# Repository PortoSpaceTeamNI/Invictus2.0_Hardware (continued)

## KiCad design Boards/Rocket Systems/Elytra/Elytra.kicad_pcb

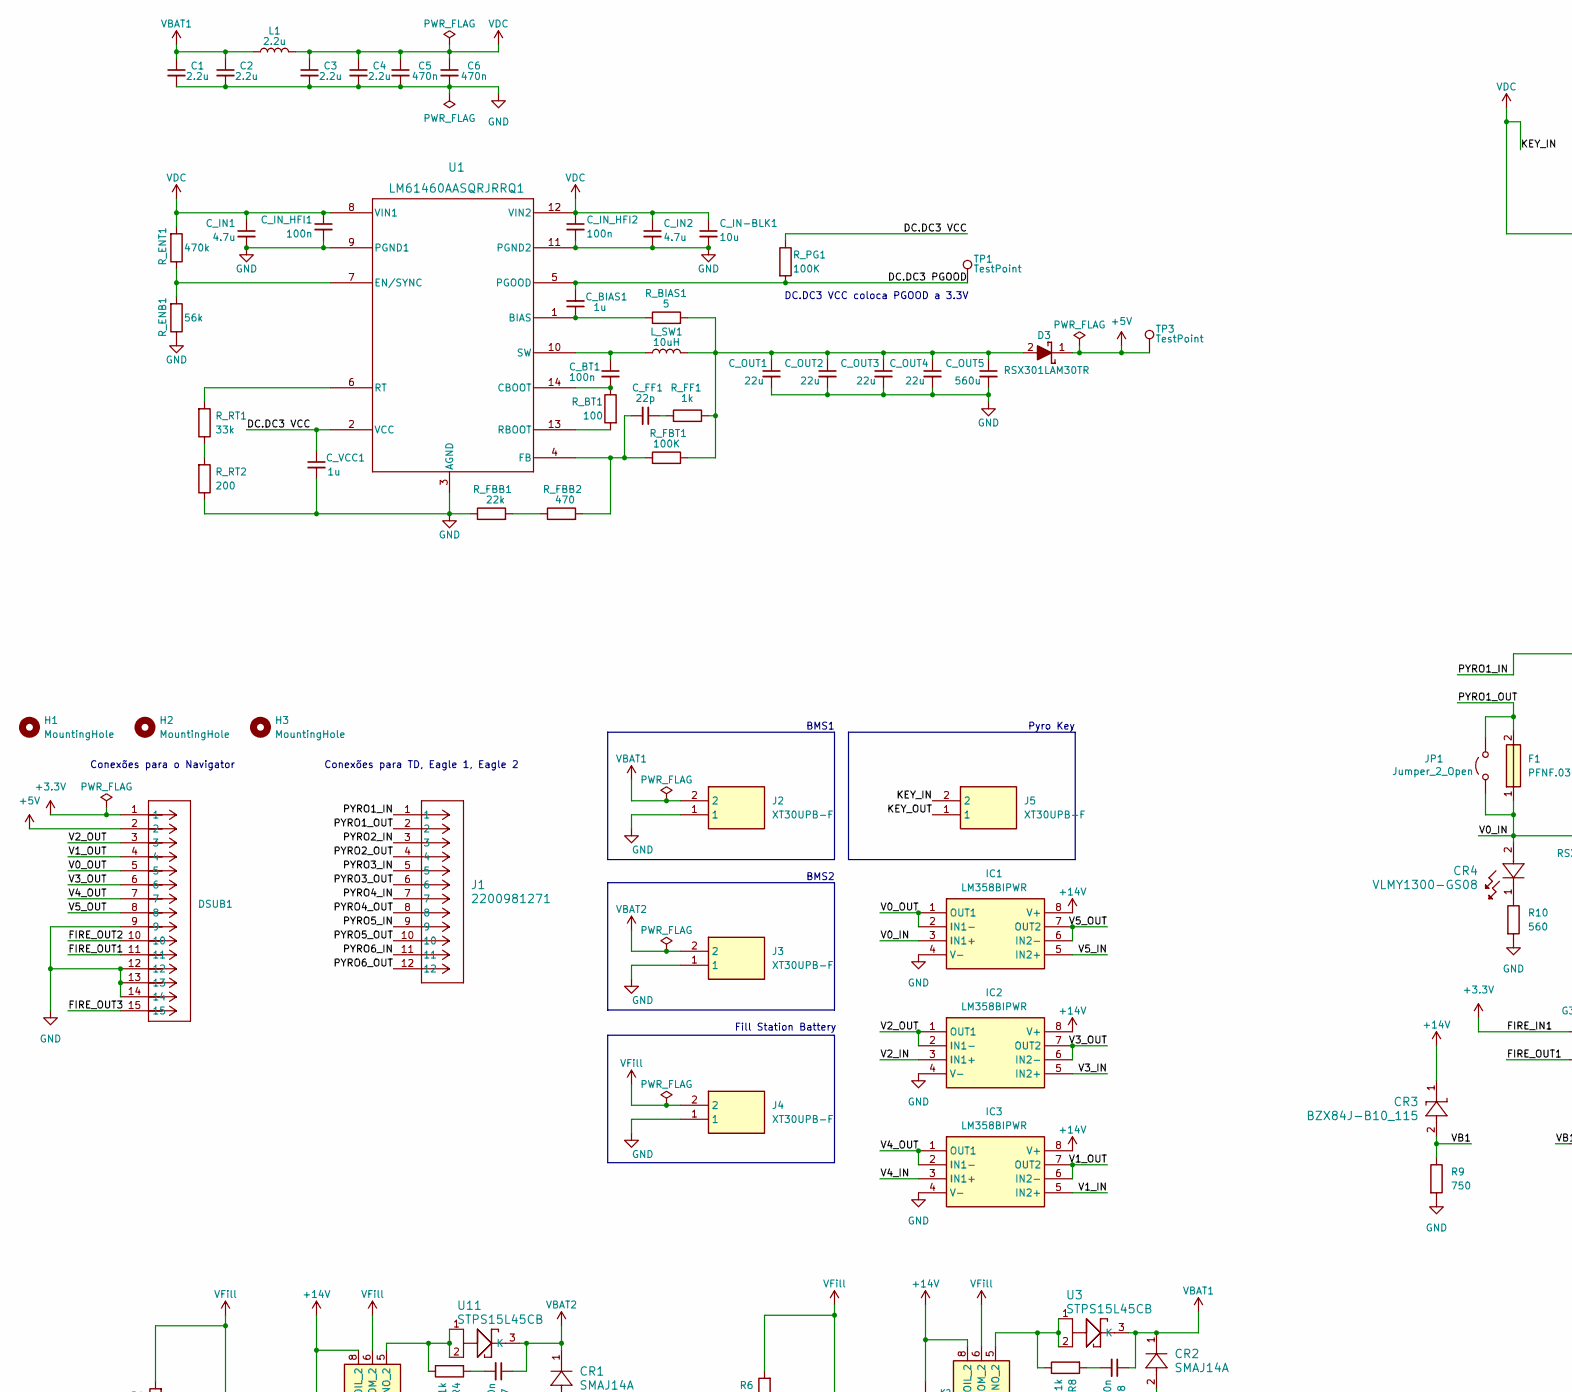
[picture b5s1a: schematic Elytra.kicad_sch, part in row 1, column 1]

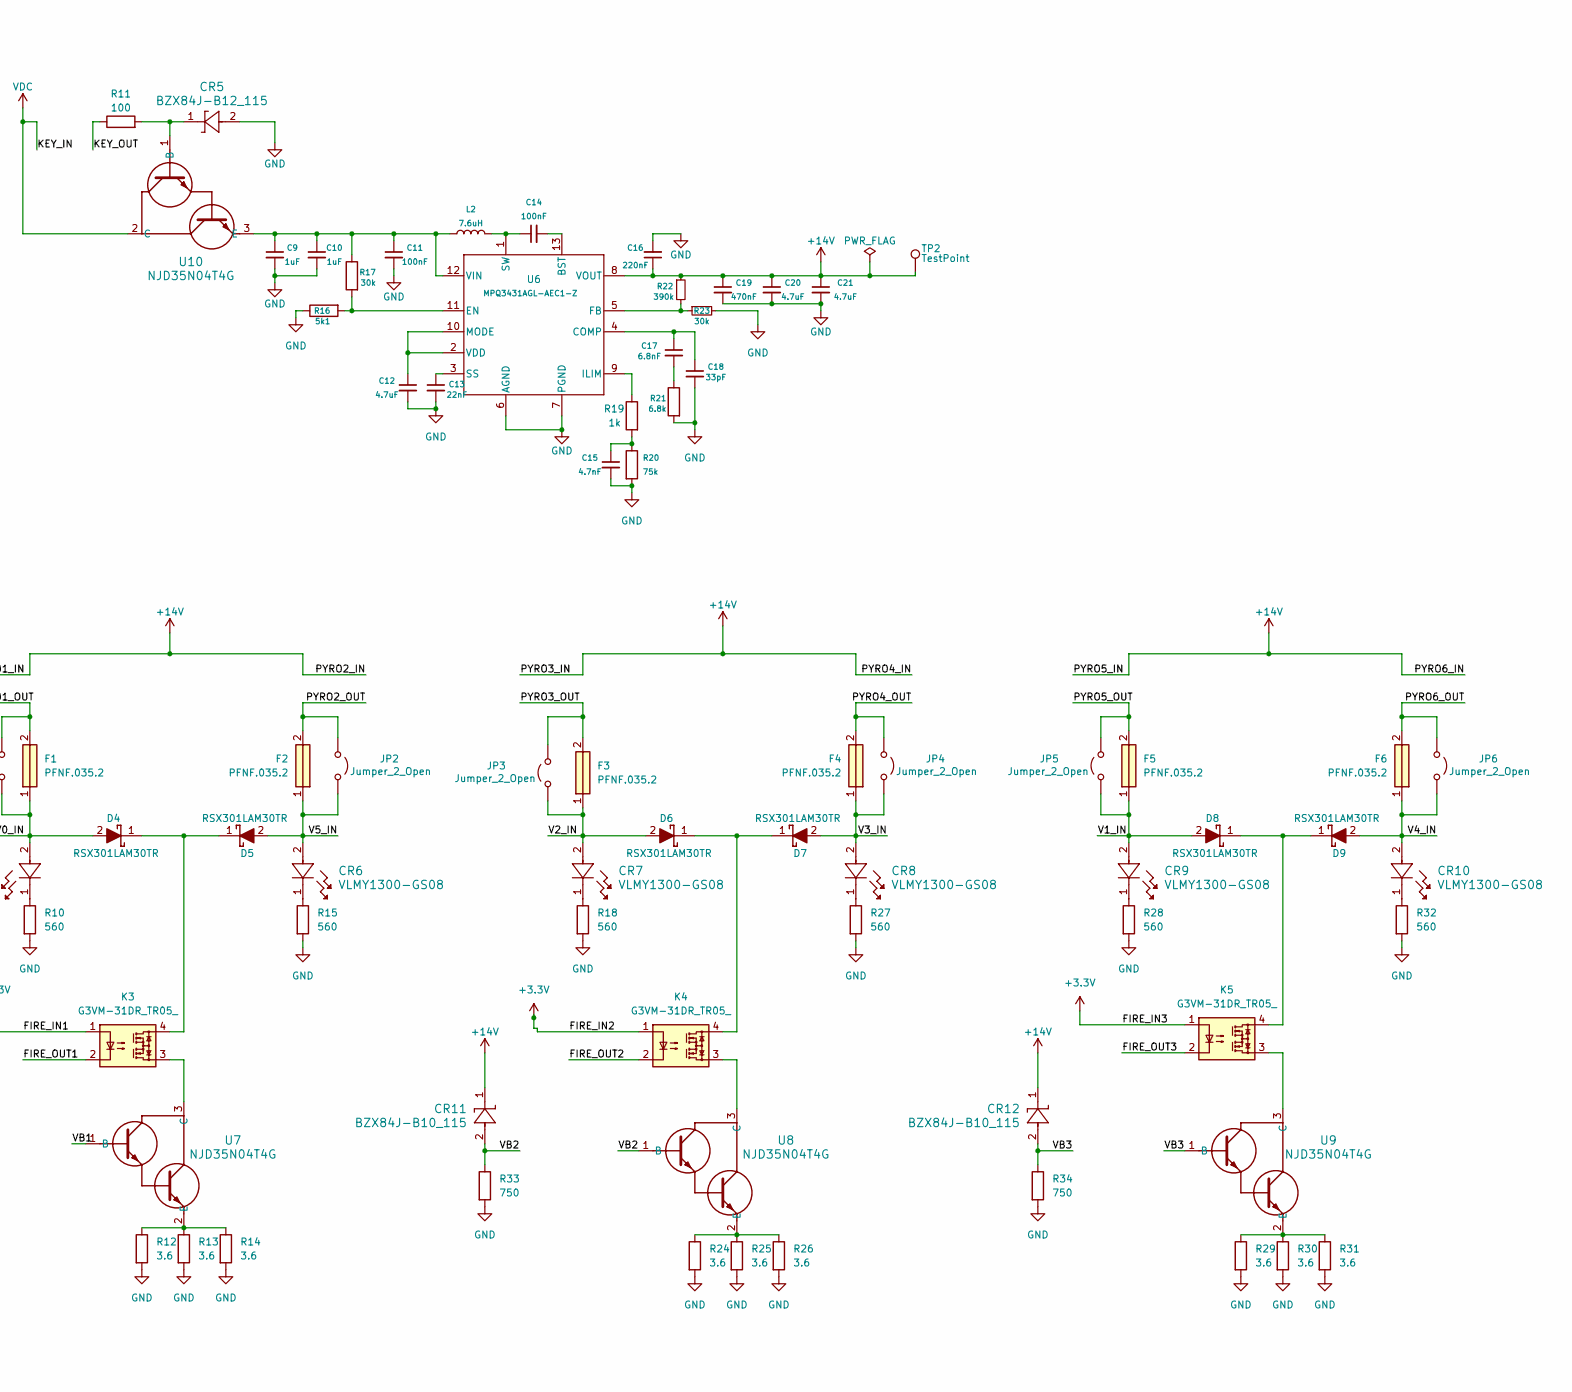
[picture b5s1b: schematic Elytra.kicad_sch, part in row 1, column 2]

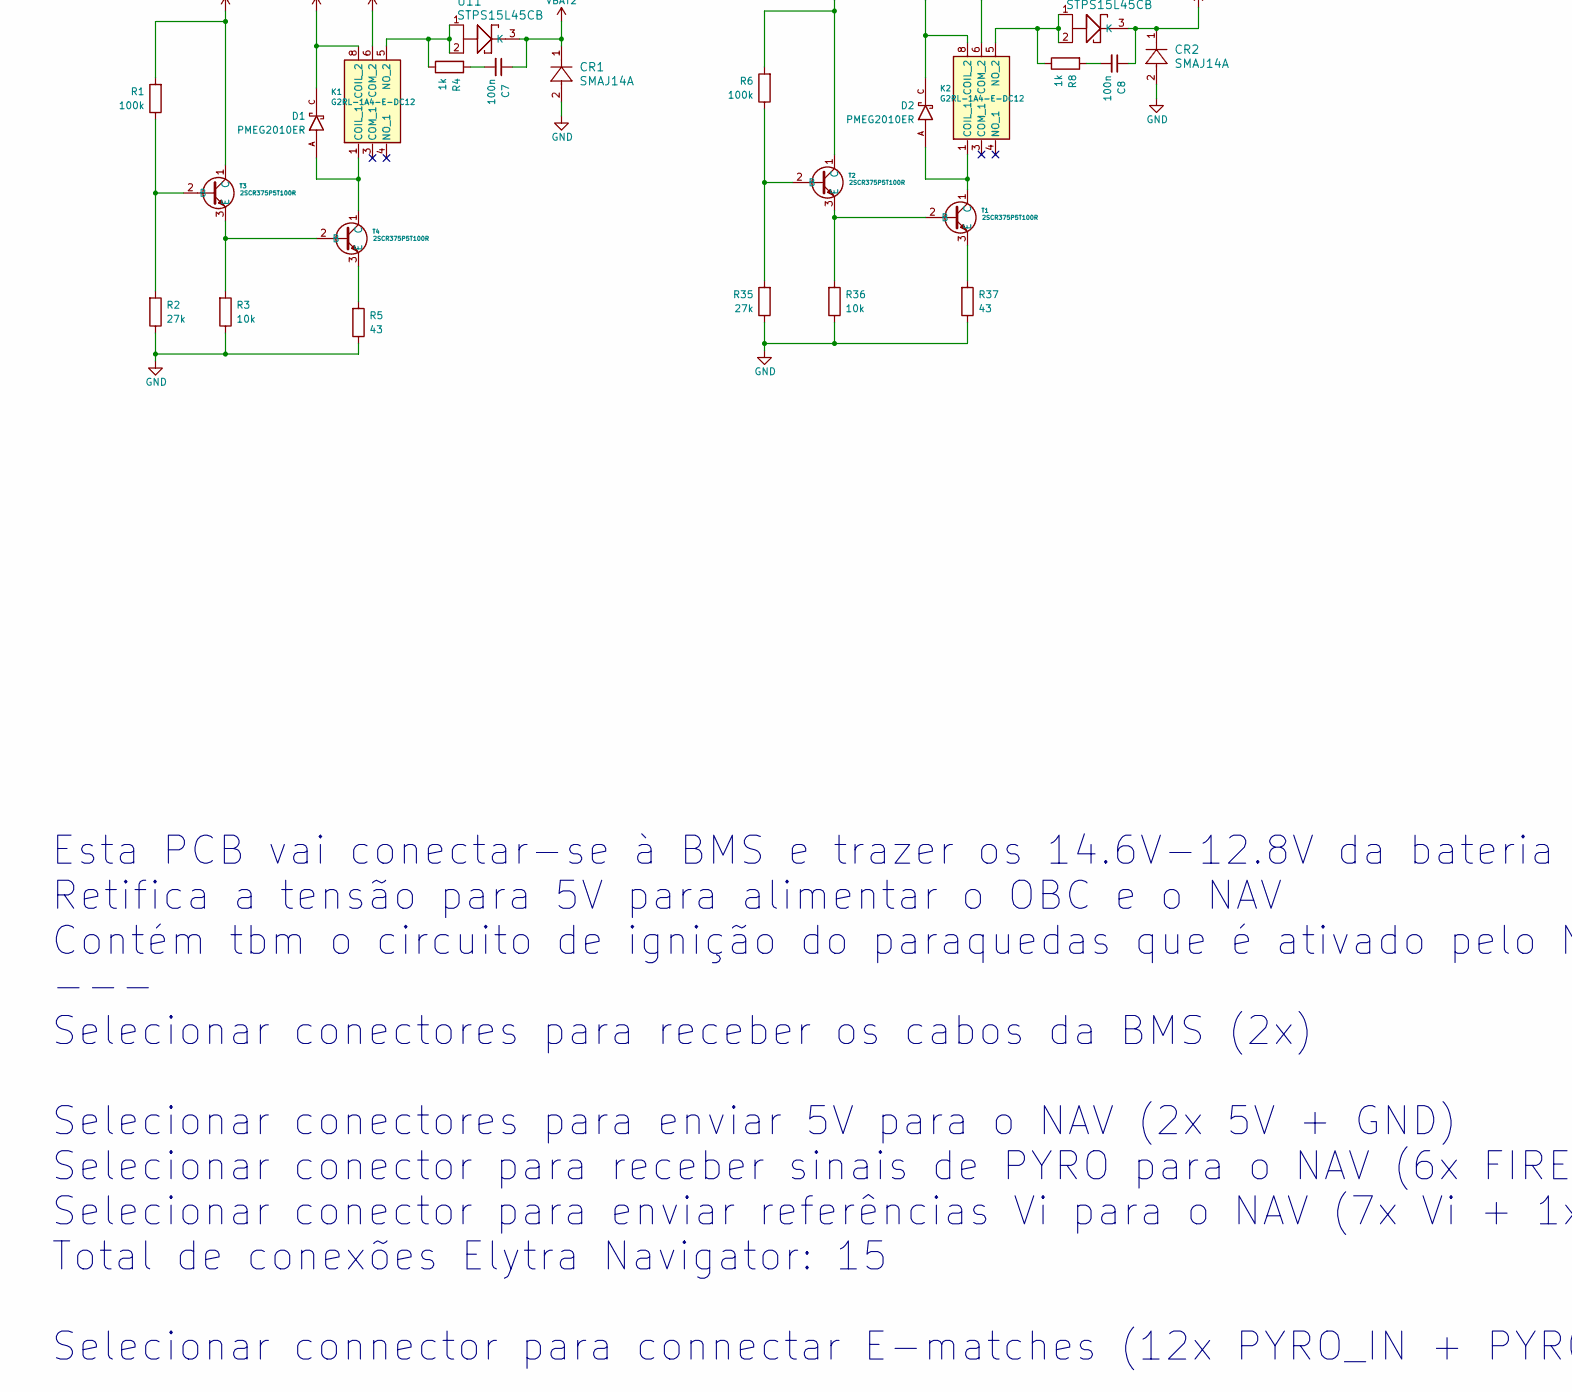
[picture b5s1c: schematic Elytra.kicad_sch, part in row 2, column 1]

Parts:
C1, C2, C3, C4: 2.2u; Capacitor_1206
C5, C6: 470n; Capacitor_1206
C7, C8: 100n; Capacitor_0603
C9, C10: 1uF; Capacitor_0603
C11, C14: 100nF; Capacitor_0603
C12: 4.7uF; Capacitor_0603
C13: 22nF; Capacitor_0603
C15: 4.7nF; Capacitor_0603
C16: 220nF; Capacitor_0603
C17: 6.8nF; Capacitor_0603
C18: 33pF; Capacitor_0603
C19: 470nF; Capacitor_0603
C20, C21: 4.7uF; Capacitor_0805
CR1, CR2: SMAJ14A; SMASeries_LTF
CR3, CR11, CR12: BZX84J-B10_115; CR_SC-90_NEX
CR4, CR6, CR7, CR8, CR9, CR10: VLMY1300-GS08; LEDC1608X100N
CR5: BZX84J-B12_115; CR_SC-90_NEX
C_BIAS1: 1u; Capacitor_0603
C_BT1: 100n; Capacitor_0603
C_FF1: 22p; Capacitor_0402
C_IN1, C_IN2: 4.7u; Capacitor_1206
C_IN-BLK1: 10u; Capacitor_4mm
C_IN_HFI1, C_IN_HFI2: 100n; Capacitor_0603
C_OUT1, C_OUT2, C_OUT3, C_OUT4: 22u; Capacitor_0805
C_OUT5: 560u; Capacitor_8mm
C_VCC1: 1u; Capacitor_0603
D1, D2: PMEG2010ER; SODFL3517X110N; PARTREV 01
D3, D4, D5, D6, D7, D8, D9: RSX301LAM30TR; DIOM5026X220N; Mouser Part Number 755-RSX301L-30DDTE25
DSUB1: HDL15-SL-B
F1, F2, F3, F4, F5, F6: PFNF.035.2; FUS1206_24N_SCH; Mouser Part Number 693-PFNF.035.2
H1, H2, H3: MountingHole; MountingHole_3.2mm_M3_ISO7380
IC1, IC2, IC3: LM358BIPWR; SOP65P640X120-8N; Mouser Part Number 595-LM358BIPWR
J1: 2200981271; CONN_2200980000-SD_12_MOL
J2, J3, J4, J5: XT30UPB-F; XT30UPBF; Manufacturer_Part_Number XT30UPB-F
JP1, JP2, JP3, JP4, JP5, JP6: Jumper_2_Open; SolderJumper-2_P1.3mm_Open_RoundedPad1.0x1.5mm
K1, K2: G2RL-1A4-E-DC12; G2RL1A4EDC12; Mouser Part Number 653-G2RL-1A4-E-DC12
K3, K4, K5: G3VM-31DR_TR05_; G3VM31DRTR05; Mouser Part Number 653-G3VM-31DR(TR05)
L1: 2.2u; IND_SPM10065VT-2R2M-D
L2: 7.6uH; IND_BOURNS_SRR1260
L_SW1: 10uH; SRP7028A3R3M
R1, R6: 100k; RES_0603
R2, R35: 27k; RES_0603
R3, R36: 10k; RES_0603
R4, R8: 1k; RES_0805
R5, R37: 43; RES_0603
R9, R33, R34: 750; RES_0805
R10, R15, R18, R27, R28, R32: 560; RES_0805
R11: 100; RES_0805
R12, R13, R14, R24, R25, R26, R29, R30, R31: 3.6; RESC3263X80N
R16: 5k1; RES_0603
R17, R23: 30k; RES_0603
R19: 1k; RES_0603
R20: 75k; RES_0603
R21: 6.8k; RES_0603
R22: 390k; RES_0603
R_BIAS1: 5; RES_0603
R_BT1: 100; RES_0603
R_ENB1: 56k; RES_0603
R_ENT1: 470k; RES_0603
R_FBB1: 22k; RES_0603
R_FBB2: 470; RES_0603
R_FBT1: 100K; RES_0603
R_FF1: 1k; RES_0603
R_PG1: 100K; RES_0603
R_RT1: 33k; RES_0603
R_RT2: 200; RES_0603
T1, T2, T3, T4: 2SCR375P5T100R; TRANS_2SA2071P_ROM
TP1, TP2, TP3: TestPoint; TestPoint_Pad_2.0x2.0mm
U1: LM61460AASQRJRRQ1; VQFN-HR14_RJR_TEX
U3, U11: STPS15L45CB; DPAK_STM
U6: MPQ3431AGL-AEC1-Z; QFN-13_MPQ3431A_MNP
U7, U8, U9, U10: NJD35N04T4G; DPAK-4_6P22X6P73_ONS

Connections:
+3.3V: DSUB1.1, K3.1, K4.1, K5.1
+5V: D3.1 (K), DSUB1.2, TP3.1
+14V: C16.1, C19.1, C20.1, C21.1, CR3.1, CR11.1, CR12.1, D1.C, D2.C, IC1.8 (V+), IC2.8 (V+), IC3.8 (V+), J1.1, J1.3, J1.5, J1.7, J1.9, J1.11, K1.8 (COIL_2), K2.8 (COIL_2), R22.1, TP2.1, U6.8 (VOUT)
/DC.DC3 PGOOD: C_BIAS1.2, R_PG1.2, TP1.1, U1.5 (PGOOD)
/DC.DC3 VCC: C_VCC1.1, R_PG1.1, U1.2 (VCC)
/FIRE_OUT1: DSUB1.11, K3.2
/FIRE_OUT2: DSUB1.10, K4.2
/FIRE_OUT3: DSUB1.15, K5.2
/KEY_OUT: J5.1, R11.1
/PYRO1_OUT: F1.2, J1.2, JP1.2 (B)
/PYRO2_OUT: F2.2, J1.4, JP2.2 (B)
/PYRO3_OUT: F3.2, J1.6, JP3.2 (B)
/PYRO4_OUT: F4.2, J1.8, JP4.2 (B)
/PYRO5_OUT: F5.2, J1.10, JP5.2 (B)
/PYRO6_OUT: F6.2, J1.12, JP6.2 (B)
/V0_IN: CR4.2, D4.2 (A), F1.1, IC1.3 (IN1+), JP1.1 (A)
/V0_OUT: DSUB1.5, IC1.1 (OUT1), IC1.2 (IN1-)
/V1_IN: CR9.2, D8.2 (A), F5.1, IC3.5 (IN2+), JP5.1 (A)
/V1_OUT: DSUB1.4, IC3.6 (IN2-), IC3.7 (OUT2)
/V2_IN: CR7.2, D6.2 (A), F3.1, IC2.3 (IN1+), JP3.1 (A)
/V2_OUT: DSUB1.3, IC2.1 (OUT1), IC2.2 (IN1-)
/V3_IN: CR8.2, D7.2 (A), F4.1, IC2.5 (IN2+), JP4.1 (A)
/V3_OUT: DSUB1.6, IC2.6 (IN2-), IC2.7 (OUT2)
/V4_IN: CR10.2, D9.2 (A), F6.1, IC3.3 (IN1+), JP6.1 (A)
/V4_OUT: DSUB1.7, IC3.1 (OUT1), IC3.2 (IN1-)
/V5_IN: CR6.2, D5.2 (A), F2.1, IC1.5 (IN2+), JP2.1 (A)
/V5_OUT: DSUB1.8, IC1.6 (IN2-), IC1.7 (OUT2)
/VB1: CR3.2, R9.1, U7.1 (B)
/VB2: CR11.2, R33.1, U8.1 (B)
/VB3: CR12.2, R34.1, U9.1 (B)
GND: C1.2, C2.2, C3.2, C4.2, C5.2, C6.2, C9.2, C10.2, C11.2, C12.2, C13.2, C15.2, C16.2, C18.2, C19.2, C20.2, C21.2, CR1.2, CR2.2, CR5.2, C_IN1.2, C_IN2.2, C_IN-BLK1.2, C_IN_HFI1.2, C_IN_HFI2.2, C_OUT1.2, C_OUT2.2, C_OUT3.2, C_OUT4.2, C_OUT5.2, C_VCC1.2, DSUB1.9, DSUB1.12, DSUB1.13, DSUB1.14, IC1.4 (V-), IC2.4 (V-), IC3.4 (V-), J2.1, J3.1, J4.1, R2.1, R3.1, R5.1, R9.2, R10.2, R12.2, R13.2, R14.2, R15.2, R16.1, R18.2, R20.2, R21.2, R23.2, R24.2, R25.2, R26.2, R27.2, R28.2, R29.2, R30.2, R31.2, R32.2, R33.2, R34.2, R35.1, R36.1, R37.1, R_ENB1.1, R_FBB1.1, R_RT2.1, U1.3 (AGND), U1.9 (PGND1), U1.11 (PGND2), U6.6 (AGND), U6.7 (PGND)
unnamed: C7.2, R4.2
unnamed: C8.2, R8.2
unnamed: C15.1, R19.2, R20.1
unnamed: C17.2, R21.1
unnamed: CR4.1, R10.1
unnamed: CR6.1, R15.1
unnamed: CR7.1, R18.1
unnamed: CR8.1, R27.1
unnamed: CR9.1, R28.1
unnamed: CR10.1, R32.1
unnamed: C_FF1.1, R_FF1.2
unnamed: C_OUT1.1, C_OUT2.1, C_OUT3.1, C_OUT4.1, C_OUT5.1, D3.2 (A), L_SW1.2, R_BIAS1.2, R_FBT1.1, R_FF1.1
unnamed: D4.1 (K), D5.1 (K), K3.4
unnamed: D6.1 (K), D7.1 (K), K4.4
unnamed: D8.1 (K), D9.1 (K), K5.4
unnamed: D1.A, K1.1 (COIL_1), T4.1 (C)
unnamed: K1.5 (NO_2), R4.1, U11.1, U11.2
unnamed: D2.A, K2.1 (COIL_1), T1.1 (C)
unnamed: K2.5 (NO_2), R8.1, U3.1, U3.2
unnamed: R_FBB1.2, R_FBB2.1
unnamed: R_RT1.1, R_RT2.2
unnamed: R36.2, T1.2 (B), T2.3 (E)
unnamed: R37.2, T1.3 (E)
unnamed: R6.1, R35.2, T2.2 (B)
unnamed: R1.1, R2.2, T3.2 (B)
unnamed: R3.2, T3.3 (E), T4.2 (B)
unnamed: R5.2, T4.3 (E)
unnamed: C_BIAS1.1, R_BIAS1.1, U1.1 (BIAS)
unnamed: C_BT1.2, R_BT1.1, U1.14 (CBOOT)
unnamed: R_ENB1.2, R_ENT1.1, U1.7 (EN/SYNC)
unnamed: C_FF1.2, R_FBB2.2, R_FBT1.2, U1.4 (FB)
unnamed: R_BT1.2, U1.13 (RBOOT)
unnamed: R_RT1.2, U1.6 (RT)
unnamed: C_BT1.1, L_SW1.1, U1.10 (SW)
unnamed: C14.2, U6.13 (BST)
unnamed: C17.1, C18.1, U6.4 (COMP)
unnamed: R16.2, R17.2, U6.11 (EN)
unnamed: R22.2, R23.1, U6.5 (FB)
unnamed: R19.1, U6.9 (ILIM)
unnamed: C12.1, U6.2 (VDD), U6.10 (MODE)
unnamed: C13.1, U6.3 (SS)
unnamed: C14.1, L2.2, U6.1 (SW)
unnamed: K3.3, U7.3 (C)
unnamed: R12.1, R13.1, R14.1, U7.2 (E)
unnamed: K4.3, U8.3 (C)
unnamed: R24.1, R25.1, R26.1, U8.2 (E)
unnamed: K5.3, U9.3 (C)
unnamed: R29.1, R30.1, R31.1, U9.2 (E)
unnamed: CR5.1, R11.2, U10.1 (B)
unnamed: C9.1, C10.1, C11.1, L2.1, R17.1, U6.12 (VIN), U10.3 (E)
VBAT1: C1.1, C2.1, C8.1, CR2.1, J2.2, L1.1, U3.3 (K)
VBAT2: C7.1, CR1.1, J3.2, U11.3 (K)
VDC: C3.1, C4.1, C5.1, C6.1, C_IN1.1, C_IN2.1, C_IN-BLK1.1, C_IN_HFI1.1, C_IN_HFI2.1, J5.2, L1.2, R_ENT1.2, U1.8 (VIN1), U1.12 (VIN2), U10.2 (C)
VFill: J4.2, K1.6 (COM_2), K2.6 (COM_2), R1.2, R6.2, T2.1 (C), T3.1 (C)

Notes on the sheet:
Fill Station Battery
Conexões para o Navigator
DC.DC3 VCC coloca PGOOD a 3.3V
BMS1
BMS2
Pyro Key
Conexões para TD, Eagle 1, Eagle 2
Esta PCB vai conectar-se à BMS e trazer os 14.6V-12.8V da bateria Retifica a tensão para 5V para alimentar o OBC e o NAV Contém tbm o circuito de ignição do paraquedas que é ativado pelo NAV --- Selecionar conectores para receber os cabos da BMS (2x) Selecionar conectores para enviar 5V para o NAV 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

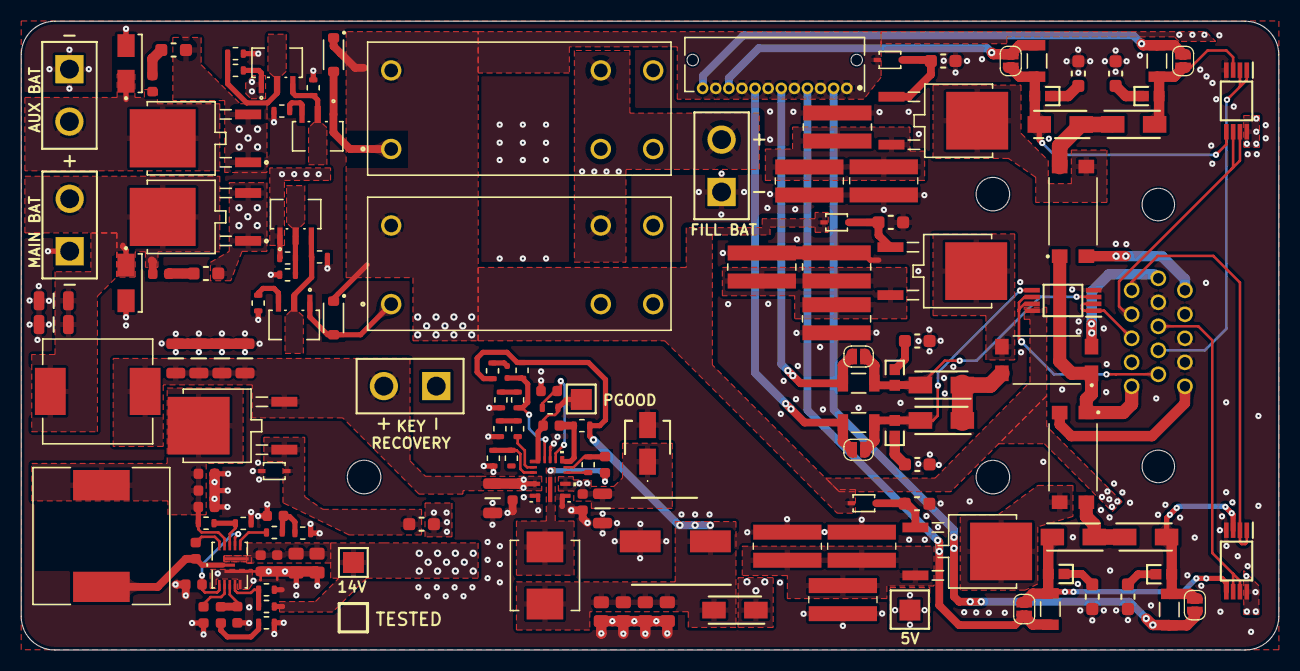
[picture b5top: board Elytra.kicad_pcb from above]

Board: 4 copper layers, 120.0 x 60.0 mm, 150 parts (0 on the bottom side), 85 nets.

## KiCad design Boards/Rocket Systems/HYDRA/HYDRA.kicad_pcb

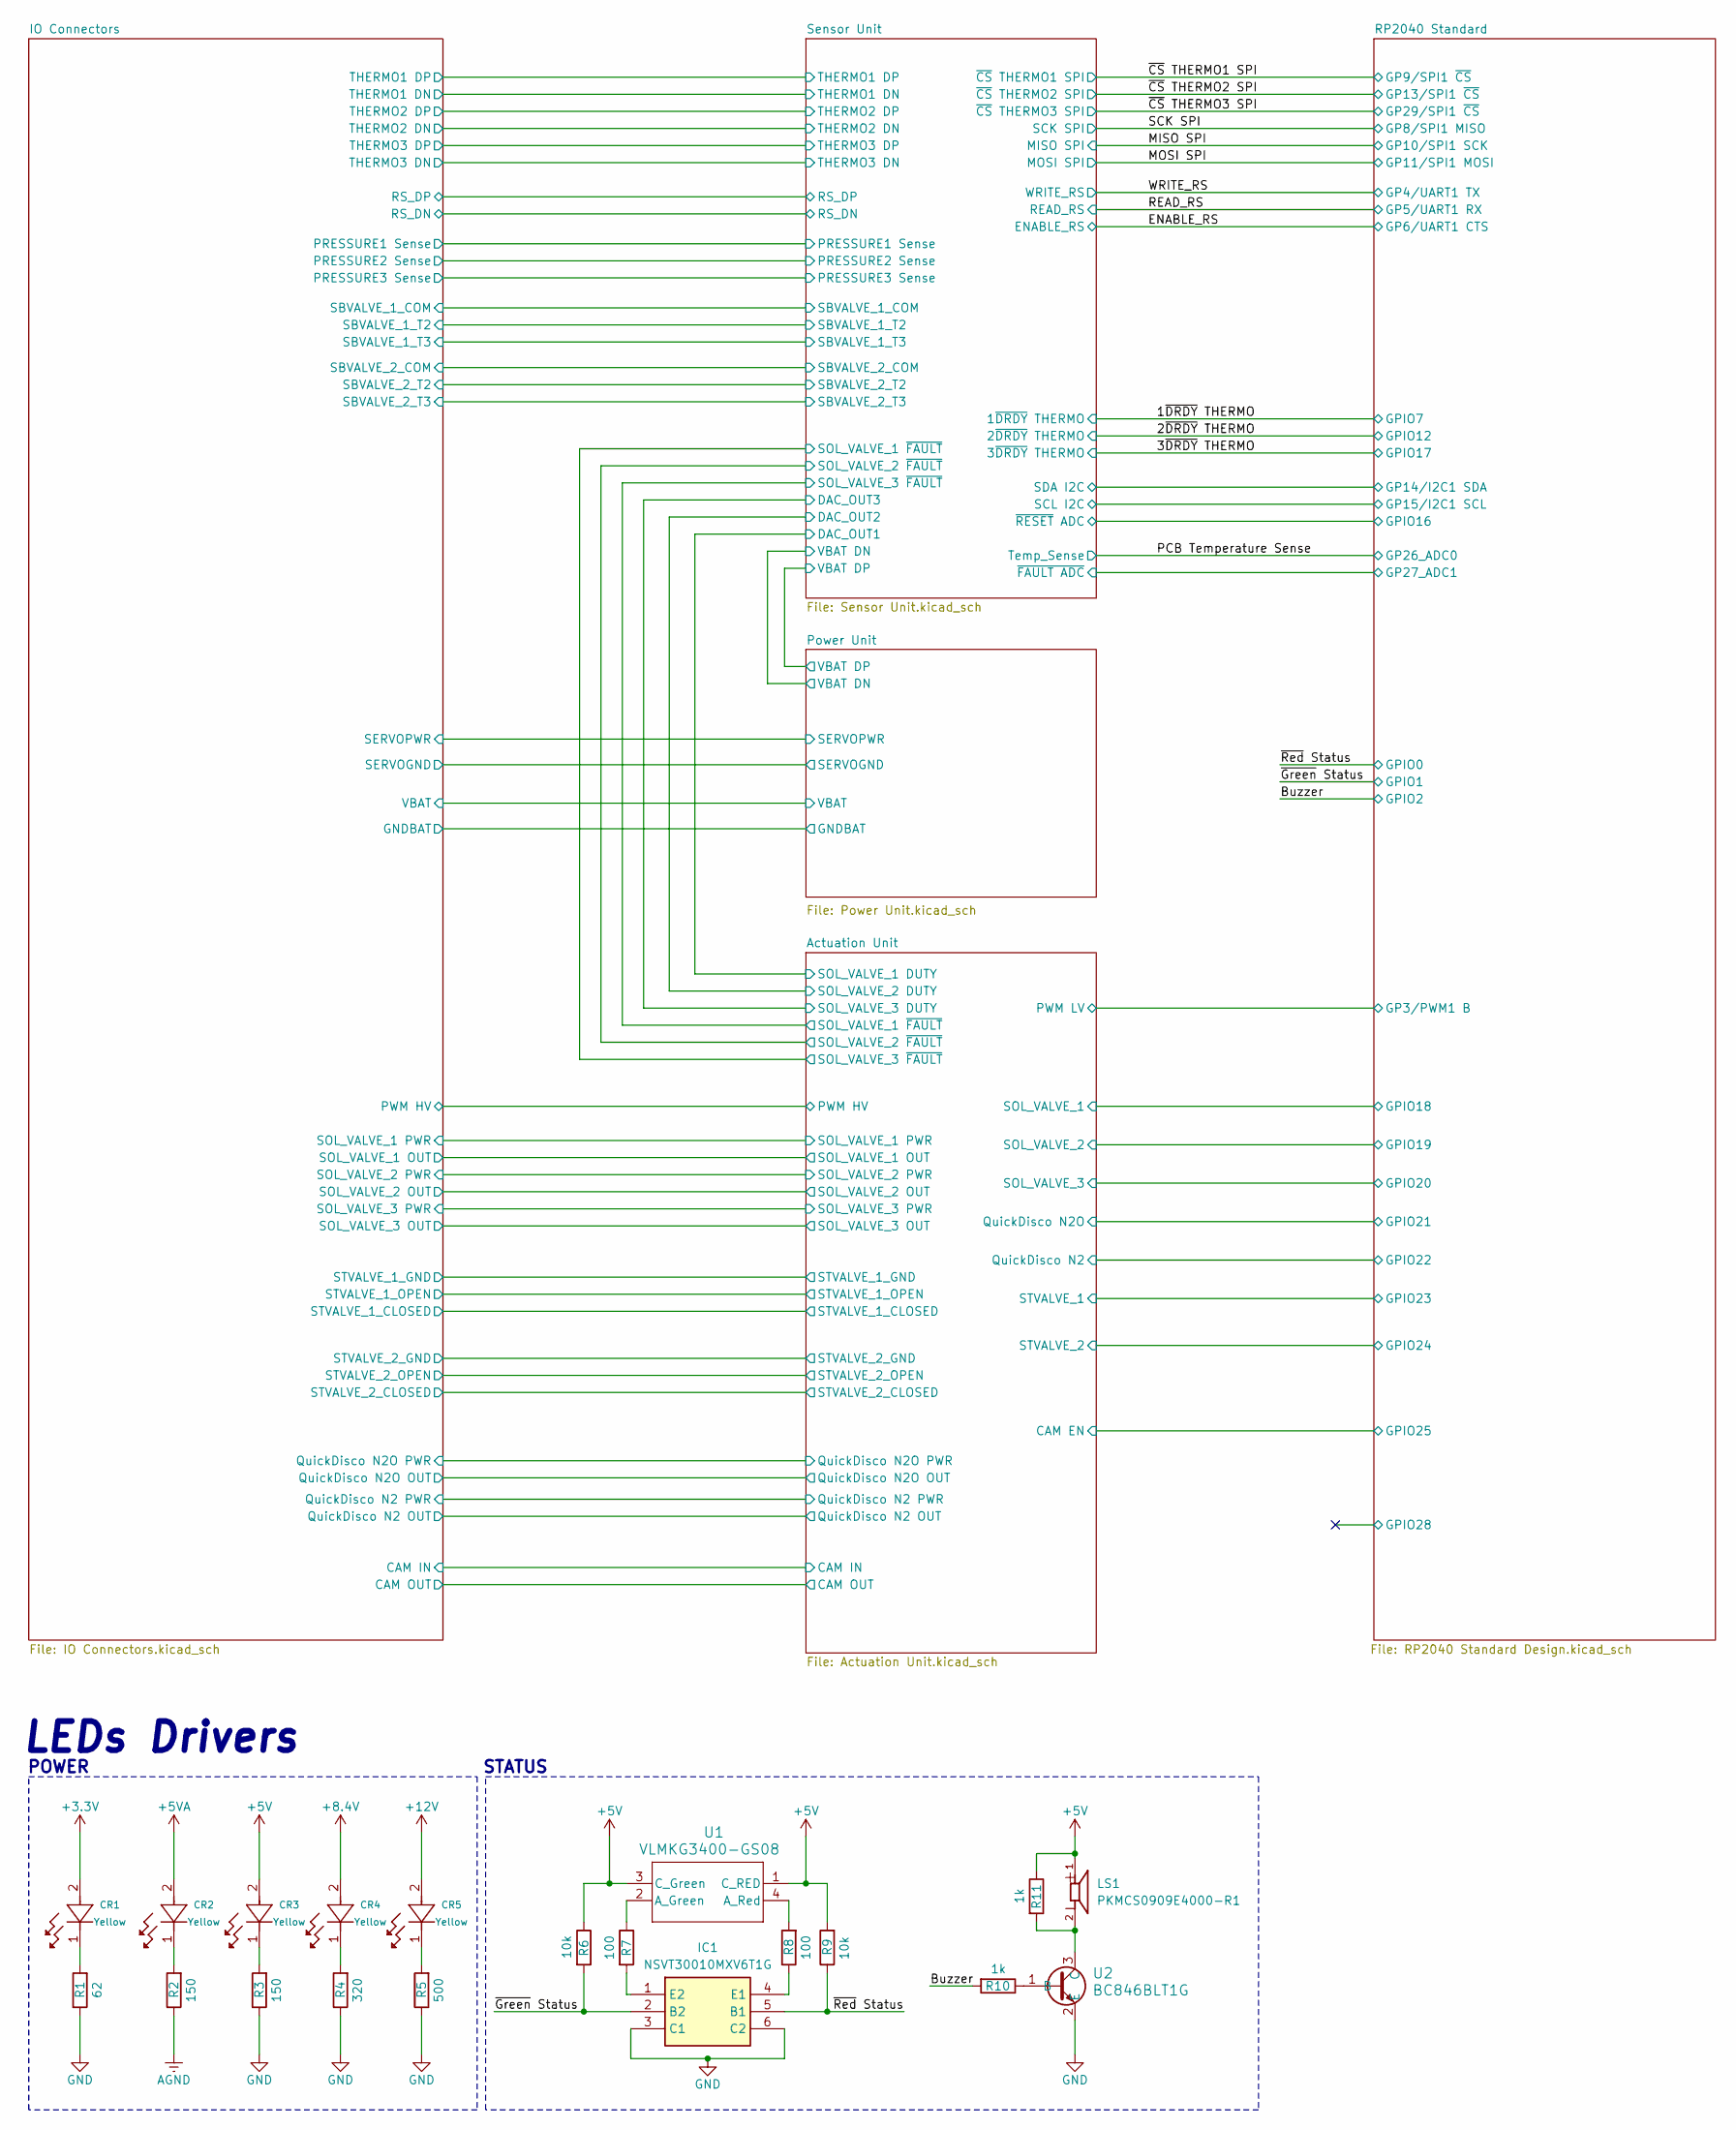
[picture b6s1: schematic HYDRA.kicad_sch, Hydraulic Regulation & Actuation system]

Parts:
CR1, CR2, CR3, CR4, CR5: VLMY1300-GS08; LEDC1608X100N
IC1: NSVT30010MXV6T1G; SOTFL50P160X60-6N; Mouser Part Number 863-NSVT30010MXV6T1G
LS1: PKMCS0909E4000-R1; SPKR_PKMCS0909E4000-R1; PARTREV May 22, 2020
R1: 62; RES_0603
R2, R3: 150; RES_0603
R4: 320; RES_0603
R5: 500; RES_0603
R6, R9: 10k; RES_0402
R7, R8: 100; RES_0603
R10, R11: 1k; RES_0603
U1: VLMKG3400-GS08; SMT_00-GS08_VIS
U2: BC846BLT1G; SOT-23_ONS

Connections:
+3.3V: CR1.2; also elsewhere on the board
+5V: CR3.2, LS1.1, R6.1, R9.2, R11.1, U1.1 (C_RED), U1.3 (C_Green); also elsewhere on the board
+5VA: CR2.2; also elsewhere on the board
+8.4V: CR4.2; also elsewhere on the board
+12V: CR5.2; also elsewhere on the board
/Buzzer: R10.2; also elsewhere on the board
/~Green Status: IC1.2 (B2), R6.2; also elsewhere on the board
/~Red Status: IC1.5 (B1), R9.1; also elsewhere on the board
AGND: R2.1; also elsewhere on the board
GND: IC1.3 (C1), IC1.6 (C2), R1.1, R3.1, R4.1, R5.1, U2.2 (E); also elsewhere on the board
unnamed: CR1.1, R1.2
unnamed: CR2.1, R2.2
unnamed: CR3.1, R3.2
unnamed: CR4.1, R4.2
unnamed: CR5.1, R5.2
unnamed: IC1.4 (E1), R8.1
unnamed: IC1.1 (E2), R7.2
unnamed: R7.1, U1.2 (A_Green)
unnamed: R8.2, U1.4 (A_Red)
unnamed: R10.1, U2.1 (B)
unnamed: LS1.2, R11.2, U2.3 (C)

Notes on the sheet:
POWER
LEDs Drivers
STATUS

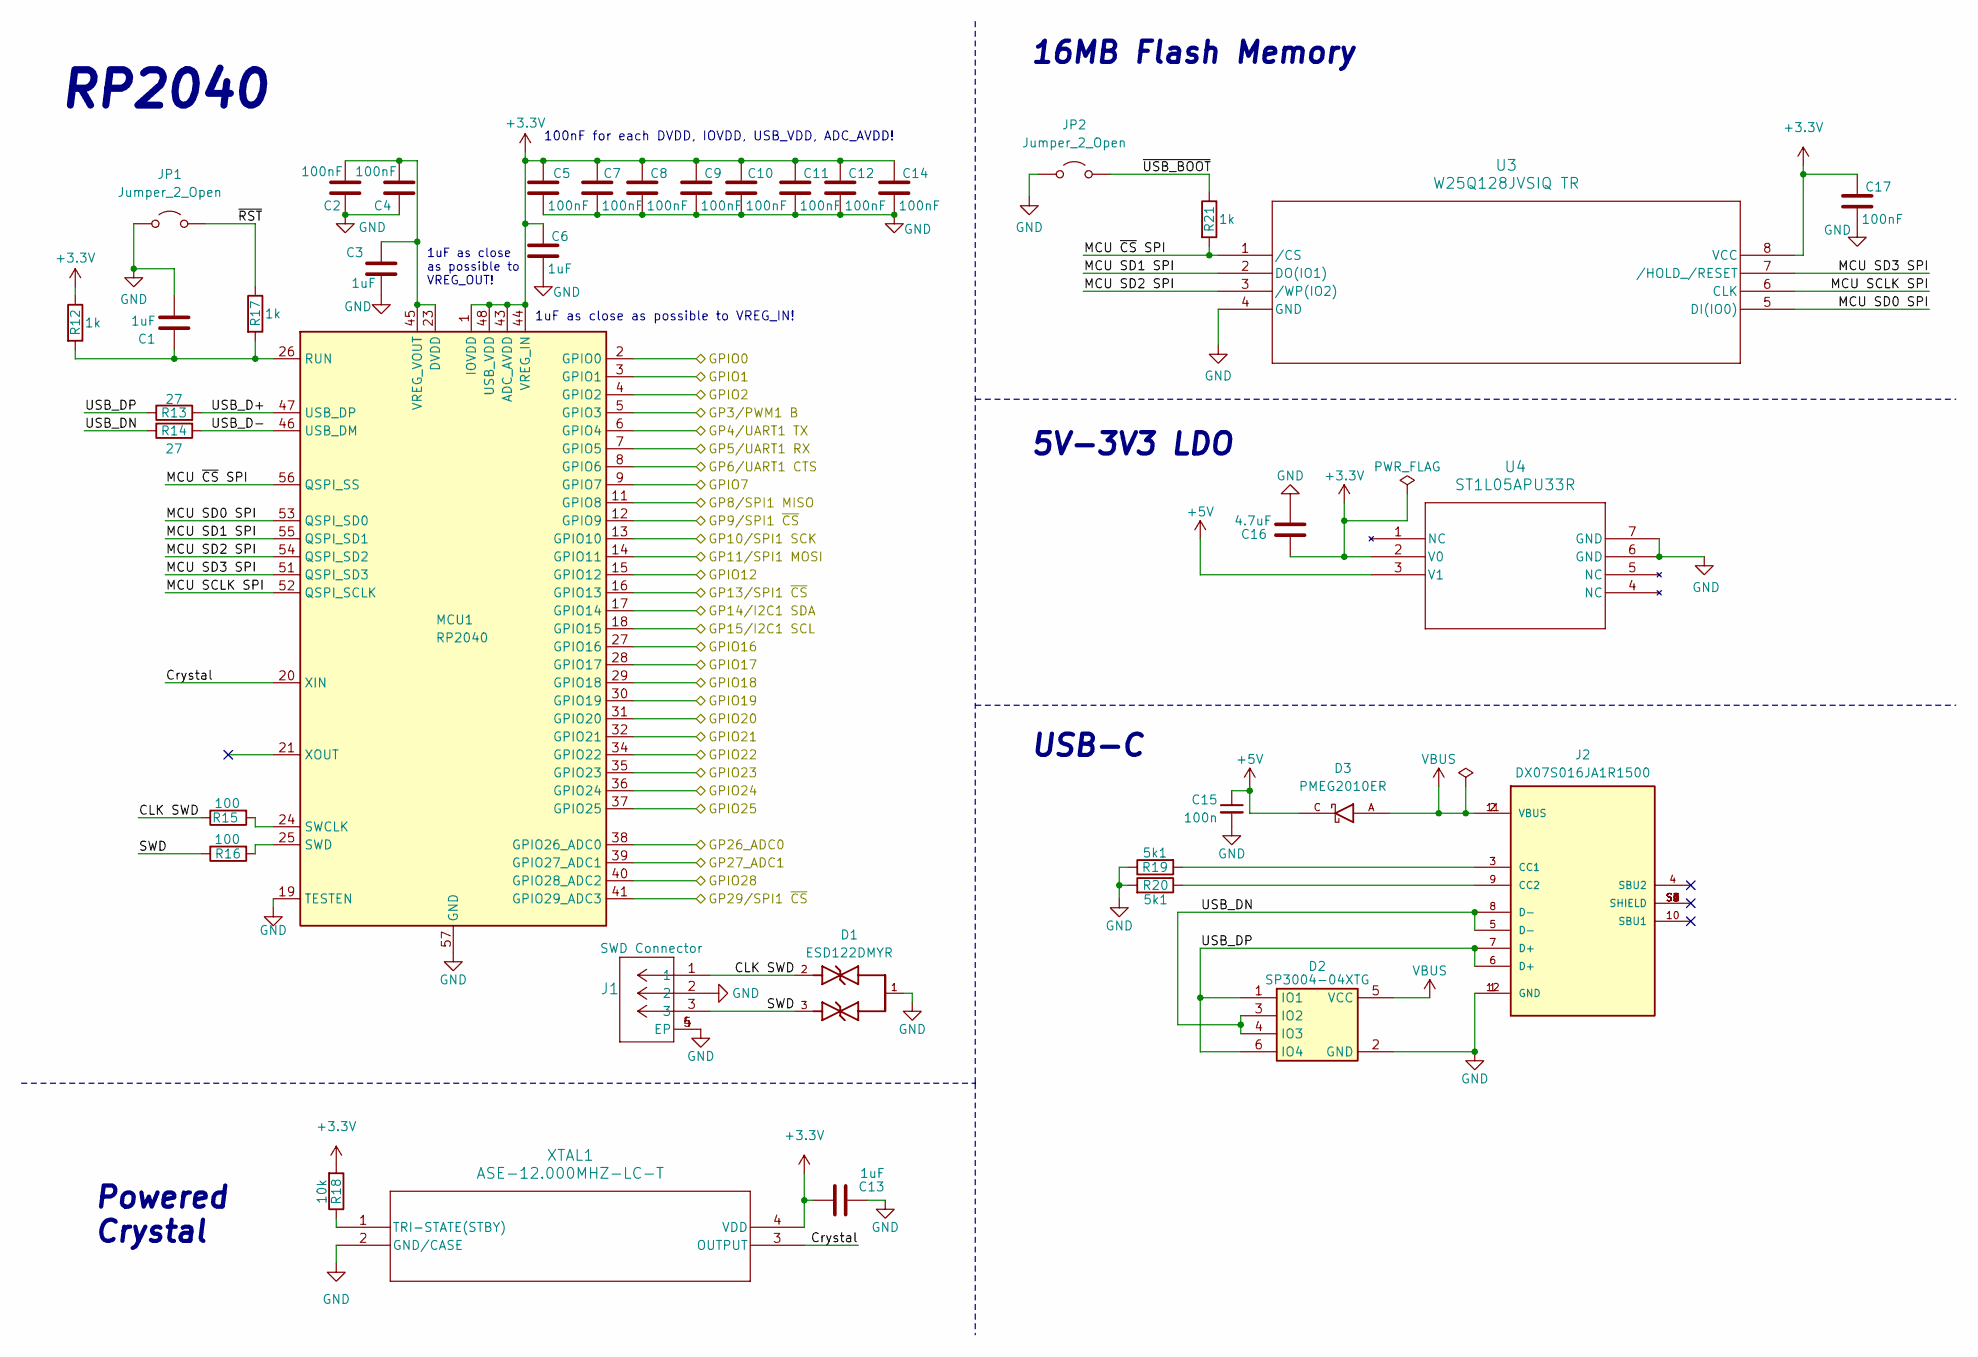
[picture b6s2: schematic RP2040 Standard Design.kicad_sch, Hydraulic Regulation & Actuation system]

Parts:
C1, C3, C6, C13: 1uF; Capacitor_0402
C2, C4, C5, C7, C8, C9, C10, C11, C12, C14, C17: 100nF; Capacitor_0402
C15: 100n; Capacitor_0402
C16: 4.7uF; Capacitor_0603
D1: ESD122DMYR; DIO_ESD122DMYR; PARTREV A
D2: SP3004-04XTG; SOT563_LTF; Mouser Part Number 576-SP3004-04XTG
D3: PMEG2010ER; SODFL3517X110N; PARTREV 01
J1: BM03B-SRSS-TBLFSN; CONN_BM03B-SRSS-TBLFSN_JST
J2: DX07S016JA1R1500; JAE_DX07S016JA1R1500; PARTREV 1
JP1, JP2: Jumper_2_Open; SolderJumper-2_P1.3mm_Open_RoundedPad1.0x1.5mm
MCU1: RP2040; QFN56_7X7_RPI
R12, R17, R21: 1k; RES_0402
R13, R14: 27; RES_0402
R15, R16: 100; RES_0402
R18: 10k; RES_0402
R19, R20: 5k1; RES_0402
U3: W25Q128JVSIQ TR; SOIC_208MIL_WIN
U4: ST1L05APU33R; DFN_5APU33R_STM
XTAL1: ASE-12.000MHZ-LC-T; ASE24576MHZLCT

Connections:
+3.3V: C5.1, C6.1, C7.1, C8.1, C9.1, C10.1, C11.1, C12.1, C13.1, C14.1, C16.2, C17.1, MCU1.1 (IOVDD), MCU1.10 (IOVDD), MCU1.22 (IOVDD), MCU1.33 (IOVDD), MCU1.42 (IOVDD), MCU1.43 (ADC_AVDD), MCU1.44 (VREG_IN), MCU1.48 (USB_VDD), MCU1.49 (IOVDD), R12.1, R18.2, U3.8 (VCC), U4.2 (V0), XTAL1.4 (VDD); also elsewhere on the board
+5V: C15.1, D3.C, U4.3 (V1); also elsewhere on the board
/1~DRDY THERMO: MCU1.9 (GPIO7); also elsewhere on the board
/2~DRDY THERMO: MCU1.15 (GPIO12); also elsewhere on the board
/3~DRDY THERMO: MCU1.28 (GPIO17); also elsewhere on the board
/Actuation Unit/CAM EN: MCU1.37 (GPIO25); also elsewhere on the board
/Actuation Unit/PWM LV: MCU1.5 (GPIO3); also elsewhere on the board
/Actuation Unit/QuickDisco N2: MCU1.34 (GPIO22); also elsewhere on the board
/Actuation Unit/QuickDisco N2O: MCU1.32 (GPIO21); also elsewhere on the board
/Actuation Unit/SOL_VALVE_1: MCU1.29 (GPIO18); also elsewhere on the board
/Actuation Unit/SOL_VALVE_2: MCU1.30 (GPIO19); also elsewhere on the board
/Actuation Unit/SOL_VALVE_3: MCU1.31 (GPIO20); also elsewhere on the board
/Actuation Unit/STVALVE_1: MCU1.35 (GPIO23); also elsewhere on the board
/Actuation Unit/STVALVE_2: MCU1.36 (GPIO24); also elsewhere on the board
/Buzzer: MCU1.4 (GPIO2); also elsewhere on the board
/ENABLE_RS: MCU1.8 (GPIO6); also elsewhere on the board
/MISO SPI: MCU1.13 (GPIO10); also elsewhere on the board
/MOSI SPI: MCU1.14 (GPIO11); also elsewhere on the board
/PCB Temperature Sense: MCU1.38 (GPIO26_ADC0); also elsewhere on the board
/READ_RS: MCU1.7 (GPIO5); also elsewhere on the board
/RP2040 Standard/CLK SWD: D1.2, J1.1, R15.1
/RP2040 Standard/Crystal: MCU1.20 (XIN), XTAL1.3 (OUTPUT)
/RP2040 Standard/GP14/I2C1 SDA: MCU1.17 (GPIO14); also elsewhere on the board
/RP2040 Standard/GP15/I2C1 SCL: MCU1.18 (GPIO15); also elsewhere on the board
/RP2040 Standard/GPIO16: MCU1.27 (GPIO16); also elsewhere on the board
/RP2040 Standard/GPIO28: MCU1.40 (GPIO28_ADC2)
/RP2040 Standard/MCU SCLK SPI: MCU1.52 (QSPI_SCLK), U3.6 (CLK)
/RP2040 Standard/MCU SD0 SPI: MCU1.53 (QSPI_SD0), U3.5 (DI(IO0))
/RP2040 Standard/MCU SD1 SPI: MCU1.55 (QSPI_SD1), U3.2 (DO(IO1))
/RP2040 Standard/MCU SD2 SPI: MCU1.54 (QSPI_SD2), U3.3 (/WP(IO2))
/RP2040 Standard/MCU SD3 SPI: MCU1.51 (QSPI_SD3), U3.7 (/HOLD_/RESET)
/RP2040 Standard/MCU ~CS SPI: MCU1.56 (QSPI_SS), R21.2, U3.1 (/CS)
/RP2040 Standard/SWD: D1.3, J1.3, R16.1
/RP2040 Standard/USB_D+: MCU1.47 (USB_DP), R13.2
/RP2040 Standard/USB_D-: MCU1.46 (USB_DM), R14.2
/RP2040 Standard/USB_DN: D2.3 (IO2), D2.4 (IO3), J2.5 (D-), J2.8 (D-), R14.1
/RP2040 Standard/USB_DP: D2.1 (IO1), D2.6 (IO4), J2.6 (D+), J2.7 (D+), R13.1
/RP2040 Standard/~RST: JP1.2 (B), R17.1
/RP2040 Standard/~USB_BOOT: JP2.2 (B), R21.1
/SCK SPI: MCU1.11 (GPIO8); also elsewhere on the board
/Sensor Unit/BUFF FB: MCU1.39 (GPIO27_ADC1); also elsewhere on the board
/WRITE_RS: MCU1.6 (GPIO4); also elsewhere on the board
/~CS THERMO1 SPI: MCU1.12 (GPIO9); also elsewhere on the board
/~CS THERMO2 SPI: MCU1.16 (GPIO13); also elsewhere on the board
/~CS THERMO3 SPI: MCU1.41 (GPIO29_ADC3); also elsewhere on the board
/~Green Status: MCU1.3 (GPIO1); also elsewhere on the board
/~Red Status: MCU1.2 (GPIO0); also elsewhere on the board
GND: C1.2, C2.1, C3.2, C4.1, C5.2, C6.2, C7.2, C8.2, C9.2, C10.2, C11.2, C12.2, C13.2, C14.2, C15.2, C16.1, C17.2, D1.1, D2.2 (GND), J1.2, J1.4 (EP), J1.5 (EP), J2.1 (GND), J2.12 (GND), JP1.1 (A), JP2.1 (A), MCU1.19 (TESTEN), MCU1.57 (GND), R19.1, R20.2, U3.4 (GND), U4.6 (GND), U4.7 (GND), XTAL1.2 (GND/CASE); also elsewhere on the board
unnamed: J2.3 (CC1), R19.2
unnamed: J2.9 (CC2), R20.1
unnamed: C1.1, MCU1.26 (RUN), R12.2, R17.2
unnamed: MCU1.24 (SWCLK), R15.2
unnamed: MCU1.25 (SWD), R16.2
unnamed: C2.2, C3.1, C4.2, MCU1.23 (DVDD), MCU1.45 (VREG_VOUT), MCU1.50 (DVDD)
unnamed: R18.1, XTAL1.1 (TRI-STATE(STBY))
VBUS: D2.5 (VCC), D3.A, J2.2 (VBUS), J2.11 (VBUS)

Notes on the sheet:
5V-3V3 LDO
USB-C
1uF as close as possible to VREG_OUT!
16MB Flash Memory
Powered Crystal
100nF for each DVDD, IOVDD, USB_VDD, ADC_AVDD!
RP2040
1uF as close as possible to VREG_IN!
